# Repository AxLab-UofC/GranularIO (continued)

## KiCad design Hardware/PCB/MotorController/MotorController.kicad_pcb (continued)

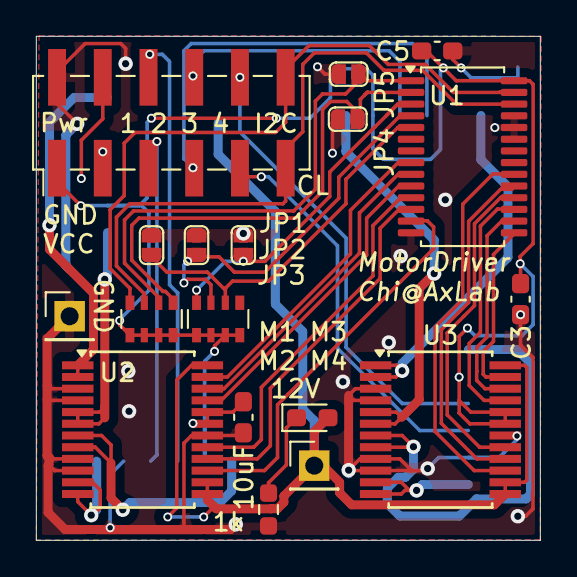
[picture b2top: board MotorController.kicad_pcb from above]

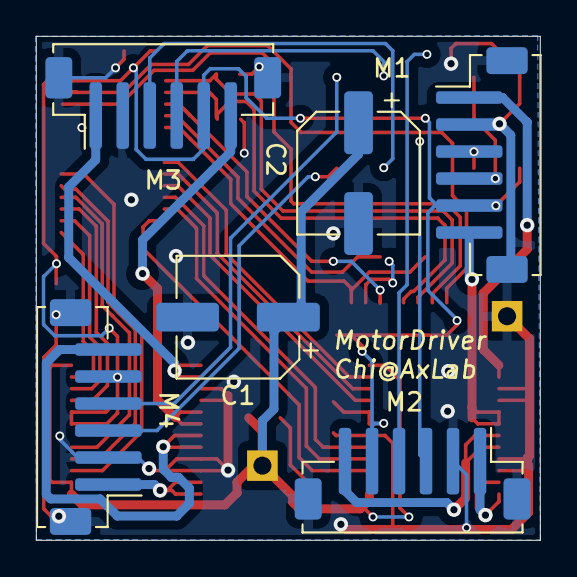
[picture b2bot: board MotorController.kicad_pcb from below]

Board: 2 copper layers, 28.0 x 28.0 mm, 24 parts (6 on the bottom side), 39 nets.

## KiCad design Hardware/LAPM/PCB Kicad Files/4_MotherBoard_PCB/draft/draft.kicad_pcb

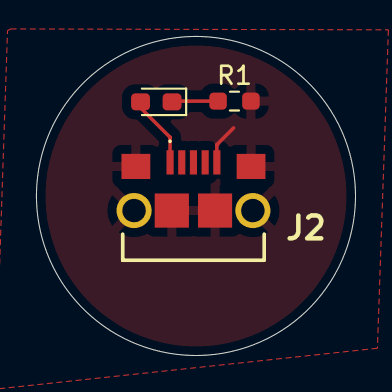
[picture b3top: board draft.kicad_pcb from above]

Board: 2 copper layers, 17.7 x 17.7 mm, 3 parts (0 on the bottom side), 3 nets.

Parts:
D1: LED; LED_0603_1608Metric_Pad1.05x0.95mm_HandSolder
J2: 10118193-0001LF; 101181930001LF
R1: 1k; R_0603_1608Metric_Pad0.98x0.95mm_HandSolder

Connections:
GND: J2.5 (GND), J2.MH1, J2.MH2, J2.MP1, J2.MP2, J2.MP3, J2.MP4, R1.2
unnamed: D1.1 (K), R1.1
VCC: D1.2 (A), J2.1 (VCC)

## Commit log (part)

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2026-06-29 Added GUI code
